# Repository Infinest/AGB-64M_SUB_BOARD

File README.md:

# AGBSUBS1-01
This KiCAD PCB project aims to recreate the original AGBSUBS1-01 sub board meant for the original AGB 64M (E201843), 128M (E201850) and 256M (E201868) dev cartridges by Nintendo. Do note however, that it is not meant to be a 1:1 copy of the original PCB.

The board supports the following save types:
- 4kbit EEPROM
-  64kbit EEPROM
-  256kbit SRAM (via FRAM chip)
-  512kbit Flash
-  1Mbit Flash

## Ordering PCBs
A ready-to-manufacture set of Gerber files can found [here](https://github.com/Infinest/AGB-64M_SUB_BOARD/blob/master/Gerbers/AGB-64M_SUB_BOARD.zip).

### Important:
Make sure to order your PCBs with a thickness of 0.6mm or they may not fit into the cartridge.
For ease of soldering any fine-pitched components (like J1) ENIG as surface finish is recommended.

## BOM:

| Reference        | Part Number           | Description  |
| ------------- |:-------------:| -----:|
| R1, R2 | RC0201FR-0710KL (or equivalent) | 10K Ω resistor 0201 (0603 metric)|
| C1, C2, C3 | GRM033R60J104KE19D (or equivalent) | 0.1µF capacitor 0201 (0603 metric)|
| U1 | FM18W08-SG | 256kbit FRAM |
| U2 | MX29L010TC-15A1 or LE26FV10N1TS / SST39VF512 or SST39LF512 | 1Mbit Flash / 512kbit Flash  |
| U3 | 9854 / 9853 | 64kbit EEPROM / 4kbit EEPROM |
| J1 | AXK640347YG | Mezzanine connector |

### Note:
Per PCB only populate **ONE** of **U1**, **U2** or **U3**
- **R2** & **C2** should be added if U1 is being populated
- **R2** & **C3** should be added if U2 is being populated
- **R1** & **C1** should be added if U3 is being populated

## Examples
### 256kbit FRAM

### 64kbit EEPROM

### 1Mbit Flash

## Additional Images:

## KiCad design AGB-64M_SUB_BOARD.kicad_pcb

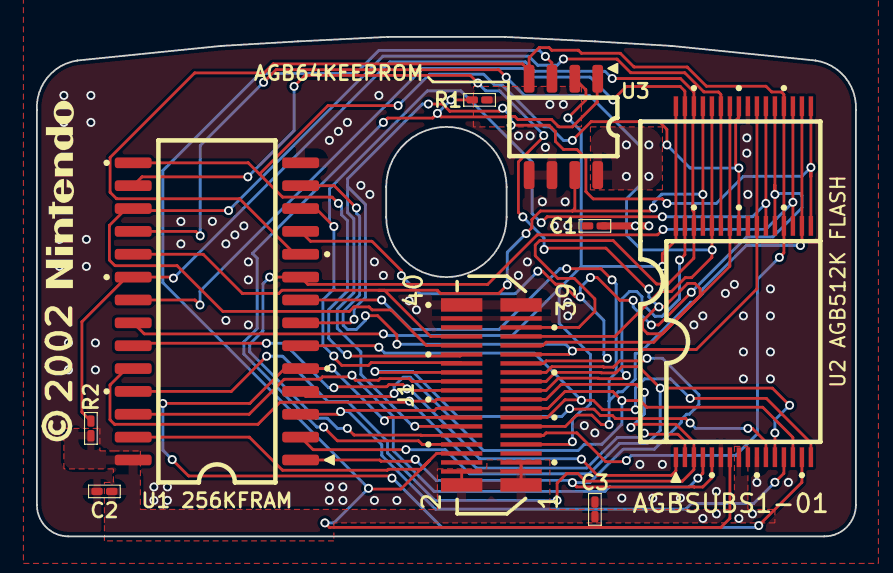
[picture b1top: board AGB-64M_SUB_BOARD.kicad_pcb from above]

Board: 2 copper layers, 45.5 x 27.8 mm, 9 parts (0 on the bottom side), 30 nets.

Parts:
C1, C2, C3: 100nF; R_0201_0603Metric_Pad0.64x0.40mm_HandSolder
J1: AXK640347YG
R1, R2: 10K; R_0201_0603Metric_Pad0.64x0.40mm_HandSolder
U1 256KFRAM: FM18W08; SOIC-28W_7.5x17.9mm_P1.27mm
U2 AGB512K FLASH: U2; AGB-TSOP-I-32
U3: SSOP-8_3.9x5.05mm_P1.27mm

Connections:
/A0: J1.11 (A0), U1 256KFRAM.10 (A0), U2 AGB512K FLASH.20 (A0), U3.4 (A0)
/A1: J1.12 (A1), U1 256KFRAM.9 (A1), U2 AGB512K FLASH.19 (A1)
/A2: J1.13 (A2), U1 256KFRAM.8 (A2), U2 AGB512K FLASH.18 (A2)
/A3: J1.14 (A3), U1 256KFRAM.7 (A3), U2 AGB512K FLASH.17 (A3)
/A4: J1.15 (A4), U1 256KFRAM.6 (A4), U2 AGB512K FLASH.16 (A4)
/A5: J1.16 (A5), U1 256KFRAM.5 (A5), U2 AGB512K FLASH.15 (A5)
/A6: J1.17 (A6), U1 256KFRAM.4 (A6), U2 AGB512K FLASH.14 (A6)
/A7: J1.18 (A7), U1 256KFRAM.3 (A7), U2 AGB512K FLASH.13 (A7)
/A8: J1.19 (A8), U1 256KFRAM.25 (A8), U2 AGB512K FLASH.3 (A8)
/A9: J1.20 (A9), U1 256KFRAM.24 (A9), U2 AGB512K FLASH.2 (A9)
/A10: J1.21 (A10), U1 256KFRAM.21 (A10), U2 AGB512K FLASH.31 (A10)
/A11: J1.22 (A11), U1 256KFRAM.23 (A11), U2 AGB512K FLASH.1 (A11)
/A12: J1.23 (A12), U1 256KFRAM.2 (A12), U2 AGB512K FLASH.12 (A12)
/A13: J1.24 (A13), U1 256KFRAM.26 (A13), U2 AGB512K FLASH.4 (A13)
/A14: J1.25 (A14), U1 256KFRAM.1 (A14), U2 AGB512K FLASH.5 (A14)
/A15: J1.26 (A15), U2 AGB512K FLASH.11 (A15)
/D0: J1.27 (D0), U1 256KFRAM.11 (D0), U2 AGB512K FLASH.21 (D0)
/D1: J1.28 (D1), U1 256KFRAM.12 (D1), U2 AGB512K FLASH.22 (D1)
/D2: J1.29 (D2), U1 256KFRAM.13 (D2), U2 AGB512K FLASH.23 (D2)
/D3: J1.30 (D3), U1 256KFRAM.15 (D3), U2 AGB512K FLASH.25 (D3)
/D4: J1.31 (D4), U1 256KFRAM.16 (D4), U2 AGB512K FLASH.26 (D4)
/D5: J1.32 (D5), U1 256KFRAM.17 (D5), U2 AGB512K FLASH.27 (D5)
/D6: J1.33 (D6), U1 256KFRAM.18 (D6), U2 AGB512K FLASH.28 (D6)
/D7: J1.34 (D7), U1 256KFRAM.19 (D7), U2 AGB512K FLASH.29 (D7), U3.7 (D7)
GND: C1.2, C2.2, C3.2, J1.37 (GND), J1.38 (GND), J1.39 (GND), J1.40 (GND), U1 256KFRAM.14 (GND), U2 AGB512K FLASH.6 (GND), U2 AGB512K FLASH.10 (GND), U2 AGB512K FLASH.24 (GND), U3.5 (GND), U3.6 (GND)
unnamed: J1.35 (CS2), R2.2, U1 256KFRAM.20 (~CE), U2 AGB512K FLASH.30 (~CE)
unnamed: J1.10 (~CS), R1.2, U3.1 (~CS)
unnamed: J1.9 (~OE), U1 256KFRAM.22 (~OE), U2 AGB512K FLASH.32 (~OE), U3.2 (~OE)
unnamed: J1.8 (~WE), U1 256KFRAM.27 (~WE), U2 AGB512K FLASH.7 (~WE), U3.3 (~WE)
VCC: C1.1, C2.1, C3.1, J1.1 (VDD), J1.2 (VDD), J1.3 (VDD), J1.4 (VDD), J1.5 (VDD), R1.1, R2.1, U1 256KFRAM.28 (VCC), U2 AGB512K FLASH.8 (VCC), U3.8 (VCC)

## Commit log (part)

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2024-09-13 Add license
